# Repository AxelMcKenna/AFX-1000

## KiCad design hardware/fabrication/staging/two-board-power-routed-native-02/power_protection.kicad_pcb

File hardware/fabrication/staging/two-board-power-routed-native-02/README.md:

# Power board — first clean copper restoration

This checkpoint restores 50 source nets while keeping all 1,090 component
values, the TBP10 schematic and all 1,105 footprint placements unchanged.
It closes **56 connections**, reducing power-board opens from **2,709 to 2,653**.
It is the current power-board development checkpoint, not a fabrication release.

| Check | Result |
| --- | --- |
| Restored tracks / through vias | 1,689 / 68 |
| Restored source terminal groups | 50, all native-connected |
| Power-board opens | 2,653 |
| Geometry / schematic parity / ERC errors | 0 / 0 / 0 |
| Retained isolated-reference ERC warnings | 2 |
| Component or placement changes | None |
| Source zones/planes imported | None |

The [native check](review.json) enables every rule category. The
[independent copper audit](copper-audit.json) compares actual source and target
track geometry, layer, width, via drill/span, net identity and native physical
pad connections. It verifies every restored connection group, all footprint
geometries and the unchanged schematic partition. It also rechecks the module
branch, 32 fault/reset cases, two source-sense channels and 64 UV cases.

## Selection and rejected trial

The source boards remain useful where every terminal of a net retains the same
translation, orientation and land shape. Nets split by the new protection
logic are excluded. Moving a single terminal excludes its old net copper from
automatic restoration; plane nets are also excluded.

The [first trial](../two-board-power-routed-native-01/review.json) restored 102
candidate nets but failed 1,046 native geometry checks. These included copper
and hole clearances, shorts, mask bridges, old track widths and old drill sizes.
All findings touched 52 candidate nets. This checkpoint excludes those complete
nets instead of weakening current rules. Their routes still require deliberate
repair or replacement. The failed trial is retained for diagnosis.

The 50 accepted nets come from supply (2), inlet (2), disconnect/protection (29),
monitor (3) and negative-startup (14) sources. The
[restoration ledger](copper-restoration.json) identifies every terminal and copper
object. Every accepted terminal set is fully connected in the native board;
that is verified separately from the constructor's selection logic.

Through vias retain their physical front/back endpoints and drill dimensions
on the provisional eight-layer board. Extra enabled inner layers change their
native layer bitmask; the audit compares the actual through-via span rather
than requiring an old six-layer bitmask. This does not qualify the physical
stack, copper weights, return paths or electrical behavior of the converted
layer arrangement. Native schematic-path annotations are excluded from the
geometry comparison; component positions, pad shapes and board setup are not.

## Actual native copper views

All eight native exports were visually inspected. The bottom view uses the
same top-view coordinates, not a mirrored assembly view. Copper-only plots
show the remaining routing clearly; they are not assembly drawings.

| Front copper | Back copper |
| --- | --- |
|  |  |

Native inner exports: [In1](plots/inner1.svg), [In2](plots/inner2.svg),
[In3](plots/inner3.svg), [In4](plots/inner4.svg), [In5](plots/inner5.svg),
[In6](plots/inner6.svg).

## Remaining fabrication work

The [TBP10 module circuit](../two-board-power-native-10/README.md) and its
[first-article procedure](../two-board-power-native-10/MODULE-FIRST-ARTICLE.md)
remain applicable. Its protection cell and return star are still unrouted.
Individual module containment, supported startup/current bounds, passive BOM,
critical placement and thermal RTN vias remain unfinished.

The [fuse voltage-budget screen](../two-board-module-protection-followup-01/review.json)
finds only 0.354 V of remaining steady-state series-drop allocation. Two reviewed
250 mA candidate fuse families exceed that at rated current; neither has been
inserted into the PCB. Actual lower-current behavior, temperature derating and
startup coordination must be supported before choosing a part or revising the
UV window. This is a design decision still to make, not an adopted fuse circuit.

The signal board remains at 251 opens with its missing ESS codec footprint.
The power board still needs 2,653 connections, final interfaces, loaded supply/
reference/enable checks and fault timing work. Manufacturing stack/BOM/process,
complete fabrication outputs, cooling/supports and full installed housing fit
also remain unfinished. No board order or fabrication release was issued.

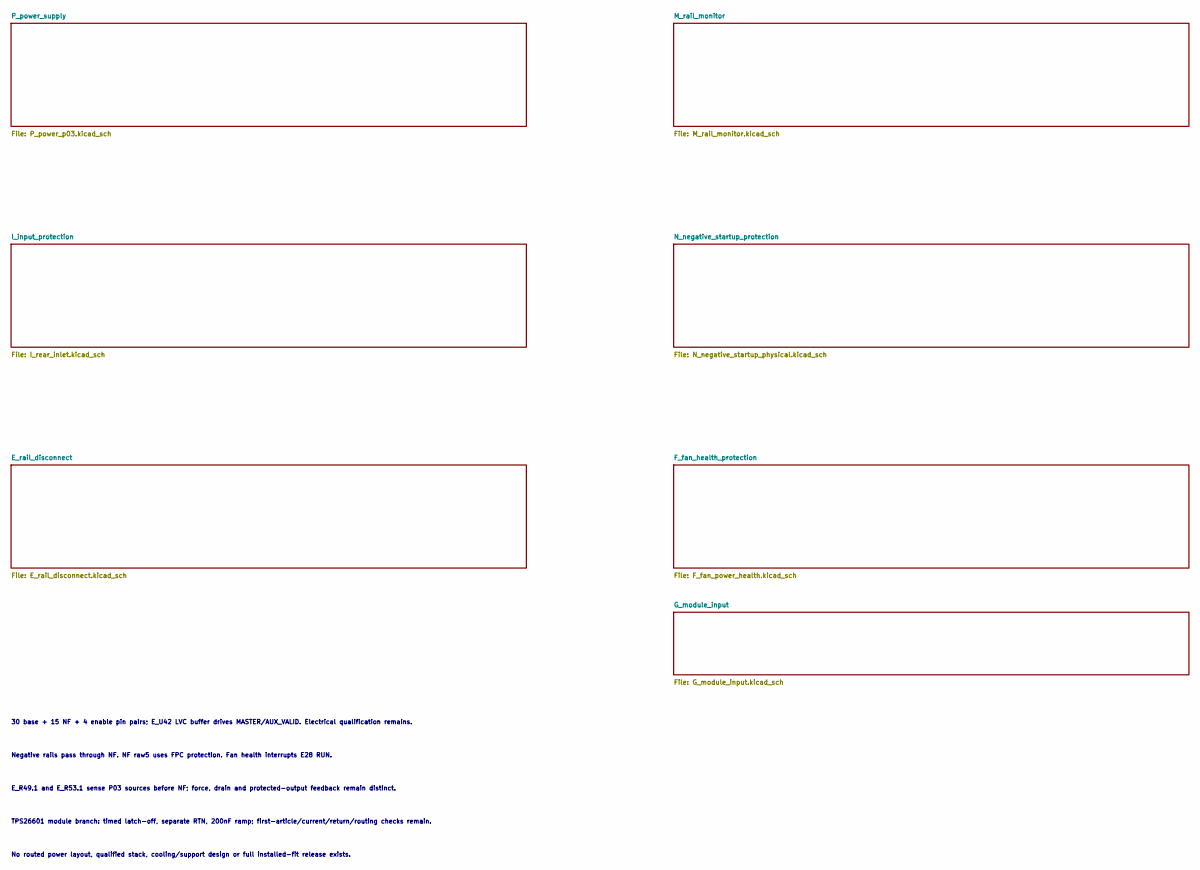
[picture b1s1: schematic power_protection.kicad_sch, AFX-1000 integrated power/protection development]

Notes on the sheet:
30 base + 15 NF + 4 enable pin pairs; E_U42 LVC buffer drives MASTER/AUX_VALID. Electrical qualification remains.
Negative rails pass through NF. NF raw5 uses FPC protection. Fan health interrupts E28 RUN.
E_R49.1 and E_R53.1 sense P03 sources before NF; force, drain and protected-output feedback remain distinct.
TPS26601 module branch: timed latch-off, separate RTN, 200nF ramp; first-article/current/return/routing checks remain.
No routed power layout, qualified stack, cooling/support design or full installed-fit release exists.

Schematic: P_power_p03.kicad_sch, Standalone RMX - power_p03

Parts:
P_C1, P_C63: 10uF 63V X7R; C_1210_3225Metric
P_C2, P_C3, P_C5, P_C6, P_C8, P_C9, P_C37, P_C42, P_C52, P_C57, P_C64, P_C65, P_C67, P_C68, P_C70, P_C204, P_C205, P_C224, P_C225, P_C254: 22uF 50V X7R 20% TDK C3225X7R1H226M250AC; C_1210_3225Metric
P_C4, P_C7, P_C10, P_C35, P_C38, P_C40, P_C43, P_C50, P_C53, P_C55, P_C58, P_C59, P_C61, P_C66, P_C69, P_C71: 100nF 50V X7R; C_0805_2012Metric
P_C11, P_C30, P_C107, P_C108: 100nF 16V X7R; C_0805_2012Metric
P_C12, P_C14, P_C73, P_C75: 68pF 50V C0G 5%; C_0805_2012Metric
P_C13, P_C15, P_C74, P_C76: 330nF 16V X7R; C_0805_2012Metric
P_C31: 2.2uF 16V X7R; C_0805_2012Metric
P_C32, P_C33: 1uF film 63V 10% MKS2C041001F00KSSD; C_Rect_L7.2mm_W5.0mm_P5.00mm
P_C34, P_C39, P_C49, P_C54, P_C240: 47nF 50V C0G 5%; C_1210_3225Metric
P_C36, P_C41, P_C51, P_C56: 10uF 50V X7R; C_1210_3225Metric
P_C60, P_C62, P_C105: 1uF 50V X7R; C_0805_2012Metric
P_C72, P_C210, P_C211, P_C230, P_C231: 100nF 50V X7R 10% TDK C1005X7R1H104K050BB; C_0402_1005Metric
P_C101, P_C102: 2.2uF 100V X7R; C_1210_3225Metric
P_C103: 220uF 35V electrolytic 20% (EEUFR1V221); CP_Radial_D8.0mm_P3.50mm
P_C104: 1uF 50V X7R; C_1210_3225Metric
P_C106: 10uF 25V X7R 10% TDK C3225X7R1E106K250AC; C_1210_3225Metric
P_C109: 1nF 16V C0G 5%; C_0805_2012Metric
P_C110: 10nF 25V C0G 5% KEMET C0603C103J3GACTU; C_0603_1608Metric
P_C113: 1uF 100V X7S 10% TDK C2012X7S2A105K125AE; C_0805_2012Metric
P_C200, P_C220: 4.7uF 25V X7R 10% TDK C2012X7R1E475K125AB; C_0805_2012Metric
P_C201, P_C221, P_C255, P_C301, P_C302: 100nF 50V X7R; C_0603_1608Metric
P_C202, P_C203, P_C222, P_C223: 2.2uF 50V X7R 10% TDK C2012X7R1H225K125AC; C_0805_2012Metric
P_C206, P_C207, P_C208, P_C209, P_C226, P_C227, P_C228, P_C229: 47uF 25V X7S 20% TDK C3225X7S1E476M250AC; C_1210_3225Metric
P_C241: 1uF 25V X7R; C_1210_3225Metric
P_C242, P_C243, P_C244, P_C245, P_C246, P_C247, P_C248, P_C249, P_C250, P_C251: 100nF 25V C0G 5% KEMET C1206C104J3GACTU; C_1206_3216Metric
P_C252, P_C253: 1uF 16V X7R; C_1210_3225Metric
P_C300: 10nF 50V C0G 5%; C_0805_2012Metric
P_C401, P_C402: 100nF 50V X7R C0603C104K5RACTU; C0603
P_C403: 10nF 50V C0G C0603C103J5GACTU; C0603
P_D1, P_D2, P_D3, P_D4, P_D103: SS16-E3/61T; D_SMA
P_D101: SMBJ33CA-E3/52; D_SMB
P_D102: BAS116,215; SOT-23
P_J2: Header6; PinHeader_1x06_P2.54mm_Vertical
P_J3: Header2; PinHeader_1x02_P2.54mm_Vertical
P_J20, P_J21, P_J23, P_J24: Wurth 7466003R M3 SMT; Wurth_7466003R
P_J22: P03 READY test; PinHeader_1x03_P2.54mm_Vertical
P_J103: Bare POWER_READY probe pads, no fitted header; Probe2_P2.54_D1
P_J104: JST B3B-XH-A (XHP-3/SXH-001T-P0.6); JST_XH_B3B-XH-A_1x03_P2.50mm_Vertical
P_J106: JST B4B-XH-A (XHP-4/SXH-001T-P0.6); JST_XH_B4B-XH-A_1x04_P2.50mm_Vertical
P_L1, P_L6: 33uH 20% SRP7050WA-330M; SRP7050WA
P_L2, P_L3, P_L7, P_L8: 68uH 20% SRP1050WA-680M; SRP1050WA
P_L20, P_L23: 4.7uH 20% Coilcraft XAL7030-472MEC; L_Coilcraft_XAL7030-472
P_Q101: PSMN012-100YL,115; LFPAK56
P_Q102: BSS138-7-F; SOT-23
P_Q103: DMN2056U-7; SOT-23
P_R1: 300k 0.01% 5ppm; R_0805_2012Metric
P_R2, P_R3, P_R4, P_R45, P_R46: 15k 0.01% 5ppm; R_0805_2012Metric
P_R5, P_R20, P_R21, P_R34, P_R35: 330k 0.01% 5ppm; R_0805_2012Metric
P_R6, P_R7, P_R49, P_R50: 4.7k 1%; R_0805_2012Metric
P_R17, P_R19, P_R110: 1k 1%; R_0805_2012Metric
P_R18, P_R120: 100k 1%; R_0805_2012Metric
P_R22, P_R27, P_R36, P_R41, P_R243, P_R244: 100k 0.01% 5ppm; R_0805_2012Metric
P_R23, P_R28, P_R37, P_R42, P_R241: 6.8k 1%; R_0805_2012Metric
P_R24, P_R38: 9.09k 1%; R_0805_2012Metric
P_R25, P_R39, P_R47, P_R306: 200k 0.01% 5ppm; R_0805_2012Metric
P_R26, P_R40, P_R308: 180k 0.01% 5ppm; R_0805_2012Metric
P_R29, P_R43: 5.62k 1%; R_0805_2012Metric
P_R44: 240k 0.01% 5ppm; R_0805_2012Metric
P_R48, P_R301, P_R303, P_R305, P_R307, P_R309, P_R314: 10k 0.01% 5ppm; R_0805_2012Metric
P_R101, P_R103, P_R117: 309k 0.1% 10ppm; R_0805_2012Metric
P_R102: 40.2k 0.1% 10ppm; R_0805_2012Metric
P_R104: 28k 0.1% 10ppm; R_0805_2012Metric
P_R105: 68.1k 0.1% 10ppm; R_0805_2012Metric
P_R106, P_R109, P_R118, P_R119: 10k 0.1% 10ppm; R_0805_2012Metric
P_R107: 4.02k 0.1% 10ppm; R_0805_2012Metric
P_R108: 11.7k 0.1% 10ppm; R_0805_2012Metric
P_R111, P_R204, P_R224, P_R246: 10k 1%; R_0805_2012Metric
P_R112, P_R114: 47k 1%; R_0805_2012Metric
P_R113: 3.3k 1%; R_0805_2012Metric
P_R115: 30.9k 0.1% 10ppm; R_0805_2012Metric
P_R116: 3.09k 0.1% 10ppm; R_0805_2012Metric
P_R121: 100 1%; R_0805_2012Metric
P_R130: 49.9 0.01% 5ppm; R_0805_2012Metric
P_R200: 9k 0.01% 2ppm Susumu RG2012L-902-L-T1; R_0805_2012Metric
P_R201: 1k 0.01% 2ppm Susumu RG2012L-102-L-T1; R_0805_2012Metric
P_R202, P_R222: 24.3k 1%; R_0805_2012Metric
P_R203, P_R223: 18.2k 0.1% 25ppm Panasonic ERA6AEB1822V; R_0805_2012Metric
P_R205, P_R225: 22k 1%; R_0805_2012Metric
P_R206: 54.9 0.1% 25ppm Panasonic ERA6AEB549V; R_0805_2012Metric
P_R220: 11k 0.01% 5ppm; R_0805_2012Metric
P_R221, P_R311: 1k 0.01% 5ppm; R_0805_2012Metric
P_R240: 100 0.01% 5ppm; R_0805_2012Metric
P_R242: 120 0.01% 5ppm; R_0805_2012Metric
P_R245: 2.21k 1%; R_0805_2012Metric
P_R300, P_R302: 87.6k 0.01% 5ppm; R_0805_2012Metric
P_R304: 324k 0.01% 5ppm; R_0805_2012Metric
P_R310: 590 0.01% 5ppm; R_0805_2012Metric
P_R312: 7.5k 0.01% 5ppm; R_0805_2012Metric
P_R313: 1M 0.01% 5ppm; R_0805_2012Metric
P_R315: 750k 0.01% 5ppm; R_0805_2012Metric
P_R316: 2.2k 0.1% 25ppm Panasonic ERA6AEB222V; R_0805_2012Metric
P_R401: 100k ohm TNPW0805100KBEEA; R0805
P_R402: 10M 1% CRCW080510M0FKEA; R0805
P_R403: 1k 1% CRCW12061K00FKEA; R1206
P_U1, P_U13: LT3471EDD#PBF; DFN-10-1EP_3x3mm_P0.5mm_EP1.65x2.38mm
P_U4: REF5025EIDR; SOIC-8_3.9x4.9mm_P1.27mm
P_U5: OPA4192ID; SOIC-14_3.9x8.7mm_P1.27mm
P_U6, P_U24: OPA2192ID; SOIC-8_3.9x4.9mm_P1.27mm
P_U7: LT3080IMS8E#PBF; MSOP-8-1EP_3x3mm_P0.65mm_EP1.68x1.88mm
P_U8: LT3080IQ#PBF; TO-263-5_TabPin3
P_U10, P_U11: LT3090IDD#PBF; DFN-10-1EP_3x3mm_P0.5mm_EP1.65x2.38mm
P_U12: LT1634AIS8-2.5#PBF; SOIC-8_3.9x4.9mm_P1.27mm
P_U20, P_U23: TPS543620RPYR; TPS543620_RPY0014A
P_U21: ADR4550BRZ; SOIC-8_3.9x4.9mm_P1.27mm
P_U22: LT3045IDD#PBF; DFN-10-1EP_3x3mm_P0.5mm_EP1.65x2.38mm
P_U25: LTC2910HGN#PBF; SSOP-16_3.9x4.9mm_P0.635mm
P_U26: SN74LVC1G97DBVR; SOT-23-6
P_U101: TPS26630RGER; Texas_RGE0024H_VQFN-24-1EP_4x4mm_P0.5mm_EP2.7x2.7mm
P_U102: TPS7A1601DGNR; MSOP-8-1EP_3x3mm_P0.65mm_EP1.68x1.88mm
P_U103: TLV7011DBVR; SOT-23-5
P_U201: TPS389001DSET; TI_DSE0006A
P_U202: SN74AUP1G17DCKR; TI_DCK0005A

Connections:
/P_power_supply/AUX_FB: P_R109.1, P_R130.2, P_U102.2 (FB)
/P_power_supply/AUX_START_DELAY: P_C110.1 (+), P_U102.7 (DELAY)
/P_power_supply/AX03_RUN_DRIVE: P_R403.1, P_U202.4 (Y)
/P_power_supply/AX03_SOURCE_CT: P_C403.1, P_U201.5 (CT)
/P_power_supply/AX03_SOURCE_RESET: P_R401.2, P_R402.1, P_U201.6 (RESET_N), P_U202.2 (A)
/P_power_supply/BLOCK_DRV: P_Q102.1 (GATE), P_U101.4 (DRV)
/P_power_supply/BLOCK_GATE: P_Q101.4 (GATE), P_Q102.3 (DRAIN), P_U101.3 (B_GATE)
/P_power_supply/CUK_NODE: P_C1.2, P_D2.2 (A), P_L3.1
/P_power_supply/FAST_OV_GATE: P_Q103.1 (GATE), P_R120.1, P_R121.2
/P_power_supply/FAST_OV_OUT: P_R117.1, P_R121.1, P_U103.1 (OUT)
/P_power_supply/FAST_OV_REF: P_C109.1 (+), P_R118.2, P_R119.1, P_U103.4 (IN-)
/P_power_supply/FAST_OV_SENSE: P_R115.2, P_R116.1, P_R117.2, P_U103.3 (IN+)
/P_power_supply/INPUT_ILIM: P_R107.1, P_U101.10 (ILIM)
/P_power_supply/INPUT_OV: P_D102.1 (ANODE), P_R103.2, P_R104.1, P_U101.7 (OVP)
/P_power_supply/INPUT_PGTH: P_R105.2, P_R106.1, P_U101.15 (PGTH)
/P_power_supply/INPUT_SLEW: P_C105.1 (+), P_U101.9 (dVdT)
/P_power_supply/INPUT_UV: P_R101.2, P_R102.1, P_U101.6 (UVLO)
/P_power_supply/LO_CUK_NODE: P_C63.2, P_D4.2 (A), P_L8.1
/P_power_supply/LO_N_FB: P_C75.2, P_R46.2, P_R47.1, P_U13.4 (FB2P)
/P_power_supply/LO_N_RMID: P_R47.2, P_R48.1
/P_power_supply/LO_N_SS: P_C76.1, P_R50.2, P_U13.7 (SHDN_SS2)
/P_power_supply/LO_N_SW: P_C63.1, P_L7.2, P_U13.6 (SW2)
/P_power_supply/LO_P_FB: P_C73.2, P_R44.2, P_R45.1, P_U13.1 (FB1N)
/P_power_supply/LO_P_SS: P_C74.1, P_R49.2, P_U13.9 (SHDN_SS1)
/P_power_supply/LO_P_SW: P_D3.2 (A), P_L6.2, P_U13.10 (SW1)
/P_power_supply/LO_REF_1V: P_C72.1, P_R46.1, P_U13.2 (FB1P), P_U13.3 (VREF)
/P_power_supply/N12_DRIVE: P_C54.1, P_R42.1, P_U6.7 (OUT)
/P_power_supply/N12_FB: P_C54.2, P_R40.2, P_R41.1, P_U6.6 (-)
/P_power_supply/N12_RMID: P_R39.2, P_R40.1
/P_power_supply/N12_SET: P_C55.1, P_R39.1, P_R42.2, P_U11.4 (SET)
/P_power_supply/N19_DRIVE: P_C49.1, P_R37.1, P_U6.1 (OUT)
/P_power_supply/N19_FB: P_C49.2, P_R35.2, P_R36.1, P_U6.2 (-)
/P_power_supply/N19_RMID: P_R34.2, P_R35.1
/P_power_supply/N19_SET: P_C50.1, P_R34.1, P_R37.2, P_U10.4 (SET)
/P_power_supply/NREF_2V5: P_R18.1, P_R19.1, P_U12.4 (GND/ANODE), P_U12.5 (TEST)
/P_power_supply/NREF_FILTER: P_C33.1, P_R19.2, P_U6.3 (+), P_U6.5 (+)
/P_power_supply/P03_ANA_DIV: P_R242.2, P_R243.1, P_R244.1
/P_power_supply/P03_ANA_DRIVE: P_C240.1 (+), P_R241.1, P_U24.1 (OUT_A)
/P_power_supply/P03_ANA_FB: P_C240.2 (-), P_R244.2, P_U24.2 (IN_A_N)
/P_power_supply/P03_ANA_SET: P_C241.1 (+), P_R241.2, P_R242.1, P_U22.7 (SET)
/P_power_supply/P03_AUX_TRIM: P_R108.2, P_R130.1
/P_power_supply/P03_A_BOOT: P_C221.1 (+), P_U23.14 (BOOT)
/P_power_supply/P03_A_BP5: P_C220.1 (+), P_U23.6 (BP5)
/P_power_supply/P03_A_ENABLE: P_R224.2, P_R225.1, P_U23.7 (EN)
/P_power_supply/P03_A_FB: P_R220.2, P_R221.1, P_U23.4 (FB)
/P_power_supply/P03_A_FSEL: P_R222.1, P_U23.1 (SYNC_FSEL)
/P_power_supply/P03_A_MODE: P_R223.1, P_U23.2 (MODE)
/P_power_supply/P03_A_SW: P_C221.2 (-), P_L23.1 (SW), P_U23.10 (SW), P_U23.13 (SW_BOOT_RETURN)
/P_power_supply/P03_D_BOOT: P_C201.1 (+), P_U20.14 (BOOT)
/P_power_supply/P03_D_BP5: P_C200.1 (+), P_U20.6 (BP5)
/P_power_supply/P03_D_ENABLE: P_R204.2, P_R205.1, P_U20.7 (EN)
/P_power_supply/P03_D_FB: P_R201.1, P_R206.2, P_U20.4 (FB)
/P_power_supply/P03_D_FB_TRIM: P_R200.2, P_R206.1
/P_power_supply/P03_D_FSEL: P_R202.1, P_U20.1 (SYNC_FSEL)
/P_power_supply/P03_D_MODE: P_R203.1, P_U20.2 (MODE)
/P_power_supply/P03_D_SW: P_C201.2 (-), P_L20.1 (SW), P_U20.10 (SW), P_U20.13 (SW_BOOT_RETURN)
/P_power_supply/P03_MON_ANA: P_R302.2, P_R303.1, P_U25.2 (V2)
/P_power_supply/P03_MON_BUCK_OK: P_U25.5 (V5), P_U26.4 (Y)
/P_power_supply/P03_MON_DIG: P_R300.2, P_R301.1, P_U25.1 (V1)
/P_power_supply/P03_MON_N12: P_R314.2, P_R315.1, P_U25.8 (V8)
/P_power_supply/P03_MON_N19: P_R312.2, P_R313.1, P_U25.7 (V7)
/P_power_supply/P03_MON_NEG_BIAS: P_R310.2, P_R311.1, P_R312.1, P_R314.1
/P_power_supply/P03_MON_P12: P_R306.2, P_R307.1, P_U25.4 (V4)
/P_power_supply/P03_MON_P19: P_R304.2, P_R305.1, P_U25.3 (V3)
/P_power_supply/P03_MON_REF: P_R310.1, P_U25.10 (REF)
/P_power_supply/P03_MON_TIMER: P_C300.1 (+), P_U25.15 (TMR)
/P_power_supply/P03_MON_VIN: P_R308.2, P_R309.1, P_U25.6 (V6)
/P_power_supply/P03_PRE6V: P_C226.1 (+), P_C227.1 (+), P_C228.1 (+), P_C229.1 (+), P_C253.1 (+), P_L23.2 (OUT), P_R220.1, P_U21.2 (VIN), P_U22.1 (IN), P_U22.2 (IN), P_U22.3 (EN_UV), P_U22.6 (PGFB)
/P_power_supply/P03_REF5: P_C252.1 (+), P_R240.1, P_U21.6 (VOUT)
/P_power_supply/P03_REF_FILTER: P_C242.1 (+), P_C243.1 (+), P_C244.1 (+), P_C245.1 (+), P_C246.1 (+), P_C247.1 (+), P_C248.1 (+), P_C249.1 (+), P_C250.1 (+), P_C251.1 (+), P_R240.2, P_U24.3 (IN_A_P)
/P_power_supply/P03_SOURCES_READY: P_R246.2, P_U20.3 (PGOOD), P_U23.3 (PGOOD), P_U26.3 (In0)
/P_power_supply/P03_SPARE_24: P_U24.6 (IN_B_N), P_U24.7 (OUT_B)
/P_power_supply/P03_SPARE_C: P_U5.8 (OUT), P_U5.9 (-)
/P_power_supply/P12_DRIVE: P_C39.1, P_R28.1, P_U5.7 (OUT)
/P_power_supply/P12_FB: P_C39.2, P_R26.2, P_R27.1, P_U5.6 (-)
/P_power_supply/P12_RMID: P_R25.2, P_R26.1
/P_power_supply/P12_SET: P_C40.1, P_R25.1, P_R28.2, P_U8.2 (SET)
/P_power_supply/P19_DRIVE: P_C34.1, P_R23.1, P_U5.1 (OUT)
/P_power_supply/P19_FB: P_C34.2, P_R21.2, P_R22.1, P_U5.2 (-)
/P_power_supply/P19_RMID: P_R20.2, P_R21.1
/P_power_supply/P19_SET: P_C35.1, P_R20.1, P_R23.2, P_U7.4 (SET)
/P_power_supply/POWER_READY: P_J22.3 (POWER_READY), P_J103.2 (POWER_READY), P_R110.2, P_R204.1, P_R224.1, P_U26.6 (In2), P_U101.16 (PGOOD)
/P_power_supply/PREF_2V5: P_C31.1, P_R17.1, P_U4.6 (VOUT)
/P_power_supply/PREF_FILTER: P_C32.1, P_R17.2, P_U5.3 (+), P_U5.5 (+)
/P_power_supply/RAW_N17: P_C56.1, P_C67.1, P_C68.1, P_C69.1, P_C75.1, P_L8.2, P_R48.2, P_U11.8 (ILIM), P_U11.9 (IN), P_U11.10 (IN), P_U11.11 (EP/IN)
/P_power_supply/RAW_N22: P_C8.1, P_C9.1, P_C10.1, P_C14.1, P_C51.1, P_C61.1, P_C62.1, P_L3.2, P_R5.2, P_R18.2, P_U6.4 (V-), P_U10.8 (ILIM), P_U10.9 (IN), P_U10.10 (IN), P_U10.11 (EP/IN)
/P_power_supply/RAW_N_FB: P_C14.2, P_R4.2, P_R5.1, P_U1.4 (FB2P)
/P_power_supply/RAW_N_SS: P_C15.1, P_R7.2, P_U1.7 (SHDN_SS2)
/P_power_supply/RAW_N_SW: P_C1.1, P_L2.2, P_U1.6 (SW2)
/P_power_supply/RAW_P17: P_C41.1, P_C64.1, P_C65.1, P_C66.1, P_C73.1, P_D3.1 (K), P_R44.1, P_U8.4 (VCONTROL), P_U8.5 (IN)
/P_power_supply/RAW_P22: P_C5.1, P_C6.1, P_C7.1, P_C12.1, P_C36.1, P_C59.1, P_C60.1, P_D1.1 (K), P_R1.1, P_U5.4 (V+), P_U7.5 (VCONTROL), P_U7.7 (IN), P_U7.8 (IN)
/P_power_supply/RAW_P_FB: P_C12.2, P_R2.2, P_R3.1, P_U1.1 (FB1N)
/P_power_supply/RAW_P_RMID: P_R1.2, P_R2.1
/P_power_supply/RAW_P_SS: P_C13.1, P_R6.2, P_U1.9 (SHDN_SS1)
/P_power_supply/RAW_P_SW: P_D1.2 (A), P_L1.2, P_U1.10 (SW1)
/P_power_supply/SPARE_OUT: P_U5.13 (SPARE-), P_U5.14 (SPARE_OUT)
/P_power_supply/SW_REF_1V: P_C11.1, P_R4.1, P_U1.2 (FB1P), P_U1.3 (VREF)
/P_power_supply/VIN_IC: P_C102.1 (+), P_C113.1 (+), P_Q101.5 (DRAIN/MB), P_R115.1, P_U101.1 (IN), P_U101.2 (IN), P_U102.5 (EN), P_U102.8 (IN)
PWR_5V_DIG_SRC: P_C30.1, P_C206.1 (+), P_C207.1 (+), P_C208.1 (+), P_C209.1 (+), P_J3.1 (5V_DIG), P_J23.1, P_L20.2 (OUT), P_R6.1, P_R7.1, P_R49.1, P_R50.1, P_R200.1, P_R300.1, P_U4.1 (EN), P_U4.2 (VIN), P_U10.5 (SHDN), P_U11.5 (SHDN); also elsewhere on the board
PWR_AGND: P_C2.2, P_C3.2, P_C4.2, P_C5.2, P_C6.2, P_C7.2, P_C8.2, P_C9.2, P_C10.2, P_C11.2, P_C13.2, P_C15.2, P_C30.2, P_C31.2, P_C32.2, P_C33.2, P_C35.2, P_C36.2, P_C37.2, P_C38.2, P_C40.2, P_C41.2, P_C42.2, P_C43.2, P_C50.2, P_C51.2, P_C52.2, P_C53.2, P_C55.2, P_C56.2, P_C57.2, P_C58.2, P_C59.2, P_C60.2, P_C61.2, P_C62.2, P_C64.2, P_C65.2, P_C66.2, P_C67.2, P_C68.2, P_C69.2, P_C70.2, P_C71.2, P_C72.2, P_C74.2, P_C76.2, P_C101.2 (-), P_C102.2 (-), P_C103.2 (-), P_C104.2 (-), P_C105.2 (-), P_C106.2 (-), P_C107.2 (-), P_C108.2 (-), P_C109.2 (-), P_C110.2 (-), P_C113.2 (-), P_C200.2 (-), P_C202.2 (-), P_C203.2 (-), P_C204.2 (-), P_C205.2 (-), P_C206.2 (-), P_C207.2 (-), P_C208.2 (-), P_C209.2 (-), P_C210.2 (-), P_C211.2 (-), P_C220.2 (-), P_C222.2 (-), P_C223.2 (-), P_C224.2 (-), P_C225.2 (-), P_C226.2 (-), P_C227.2 (-), P_C228.2 (-), P_C229.2 (-), P_C230.2 (-), P_C231.2 (-), P_C241.2 (-), P_C242.2 (-), P_C243.2 (-), P_C244.2 (-), P_C245.2 (-), P_C246.2 (-), P_C247.2 (-), P_C248.2 (-), P_C249.2 (-), P_C250.2 (-), P_C251.2 (-), P_C252.2 (-), P_C253.2 (-), P_C254.2 (-), P_C255.2 (-), P_C300.2 (-), P_C301.2 (-), P_C302.2 (-), P_C401.2, P_C402.2, P_C403.2, P_D2.1 (K), P_D4.1 (K), P_D101.2, P_D103.2 (ANODE), P_J2.2 (AGND), P_J3.2 (AGND), P_J20.1, P_J21.1, P_J22.2 (AGND), P_J103.1 (AGND), P_J104.3 (AGND), P_J106.2 (AGND), P_Q103.2 (SOURCE), P_R3.2, P_R22.2, P_R24.2, P_R27.2, P_R29.2, P_R36.2, P_R38.2, P_R41.2, P_R43.2, P_R45.2, P_R102.2, P_R104.2, P_R106.2, P_R107.2, P_R109.2, P_R111.2, P_R112.2, P_R114.2, P_R116.2, P_R119.2, P_R120.2, P_R201.2, P_R202.2, P_R203.2, P_R205.2, P_R221.2, P_R222.2, P_R223.2, P_R225.2, P_R243.2, P_R245.2, P_R301.2, P_R303.2, P_R305.2, P_R307.2, P_R309.2, P_R311.2, P_R402.2, P_U1.5 (FB2N), P_U1.11 (GND_EP), P_U4.4 (GND), P_U5.10 (+), P_U5.11 (V-), P_U5.12 (SPARE+), P_U6.8 (V+), P_U10.3 (GND), P_U11.3 (GND), P_U12.6 (VOUT/CATHODE), P_U13.5 (FB2N), P_U13.11 (GND_EP), P_U20.5 (AGND), P_U20.9 (PGND), P_U20.11 (PGND), P_U21.4 (GND), P_U22.5 (ILIM), P_U22.8 (GND), P_U22.11 (EP_GND), P_U23.5 (AGND), P_U23.9 (PGND), P_U23.11 (PGND), P_U24.4 (V_N), P_U24.5 (IN_B_P), P_U25.9 (GND), P_U25.13 (DIS), P_U25.14 (SEL), P_U26.1 (In1_AND_CONFIG_LOW), P_U26.2 (GND), P_U101.8 (GND), P_U101.25 (EP/GND), P_U102.4 (GND), P_U102.9 (EP/GND), P_U103.2 (VEE), P_U201.2 (GND), P_U202.3 (GND); also elsewhere on the board
PWR_DC_IN: P_C101.1 (+), P_D101.1, P_Q101.1 (SOURCE), P_Q101.2 (SOURCE), P_Q101.3 (SOURCE), P_Q102.2 (SOURCE), P_R101.1, P_R103.1, P_U101.5 (IN_SYS); also elsewhere on the board
PWR_MODULE_FEED_IN: P_C2.1, P_C3.1, P_C4.1, P_C70.1, P_C71.1, P_C103.1 (+), P_C104.1 (+), P_C202.1 (+), P_C203.1 (+), P_C204.1 (+), P_C205.1 (+), P_C210.1 (+), P_C211.1 (+), P_C222.1 (+), P_C223.1 (+), P_C224.1 (+), P_C225.1 (+), P_C230.1 (+), P_C231.1 (+), P_C255.1 (+), P_D103.1 (CATHODE), P_L1.1, P_L2.1, P_L6.1, P_L7.1, P_R105.1, P_R114.1, P_R308.1, P_U1.8 (VIN), P_U13.8 (VIN), P_U20.8 (VIN), P_U20.12 (VIN), P_U23.8 (VIN), P_U23.12 (VIN), P_U24.8 (V_P), P_U101.17 (OUT), P_U101.18 (OUT); also elsewhere on the board
PWR_N12_SOURCE: P_C57.1, P_C58.1, P_J2.5 (N12), P_R43.1, P_R315.2, P_U11.1 (OUT), P_U11.2 (OUT); also elsewhere on the board
PWR_N19_SOURCE: P_C52.1, P_C53.1, P_J2.3 (N19), P_R38.1, P_R313.2, P_U10.1 (OUT), P_U10.2 (OUT); also elsewhere on the board
PWR_P03_SOURCES_READY: P_J22.1 (ALL_SOURCES_READY), P_J106.4 (SOURCE_READY), P_R316.2, P_U25.12 (RST_ACTIVE_LOW); also elsewhere on the board
PWR_P12_SRC: P_C42.1, P_C43.1, P_J2.4 (P12), P_R29.1, P_R306.1, P_U8.3 (OUT/TAB); also elsewhere on the board
PWR_P19_SRC: P_C37.1, P_C38.1, P_J2.1 (P19), P_R24.1, P_R304.1, P_U7.1 (OUT), P_U7.2 (OUT), P_U7.3 (OUT), P_U7.9 (EP/OUT); also elsewhere on the board
PWR_POWER_RUN: P_J104.2 (POWER_RUN), P_Q103.3 (DRAIN), P_R112.1, P_U101.12 (SHDN), P_U102.3 (PG), P_U201.1 (SENSE); also elsewhere on the board
PWR_RUN_BEFORE_FAN: P_J106.3 (POWER_RUN), P_R403.2; also elsewhere on the board
PWR_SWITCH_SUPPLY: P_J104.1 (SWITCH_SUPPLY), P_R113.2; also elsewhere on the board
PWR_V2V5_AUX: P_C106.1 (+), P_C107.1 (+), P_C108.1 (+), P_C301.1 (+), P_C302.1 (+), P_C401.1, P_C402.1, P_D102.3 (CATHODE), P_J106.1 (V2V5_AUX), P_R108.1, P_R110.1, P_R111.1, P_R113.1, P_R118.1, P_R246.1, P_R316.1, P_R401.1, P_U25.16 (VCC), P_U26.5 (VCC), P_U102.1 (OUT), P_U103.5 (VCC), P_U201.3 (MR), P_U201.4 (VDD), P_U202.5 (VCC); also elsewhere on the board
PWR_V5_REG_SRC: P_C254.1 (+), P_J2.6 (V5_REG), P_J24.1, P_R245.1, P_R302.1, P_U22.9 (OUTS), P_U22.10 (OUT); also elsewhere on the board

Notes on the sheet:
AX03 prototype: only J106.3 buffered; internal POWER_RUN, R113 and PG topology retained. No physical/fabrication release.

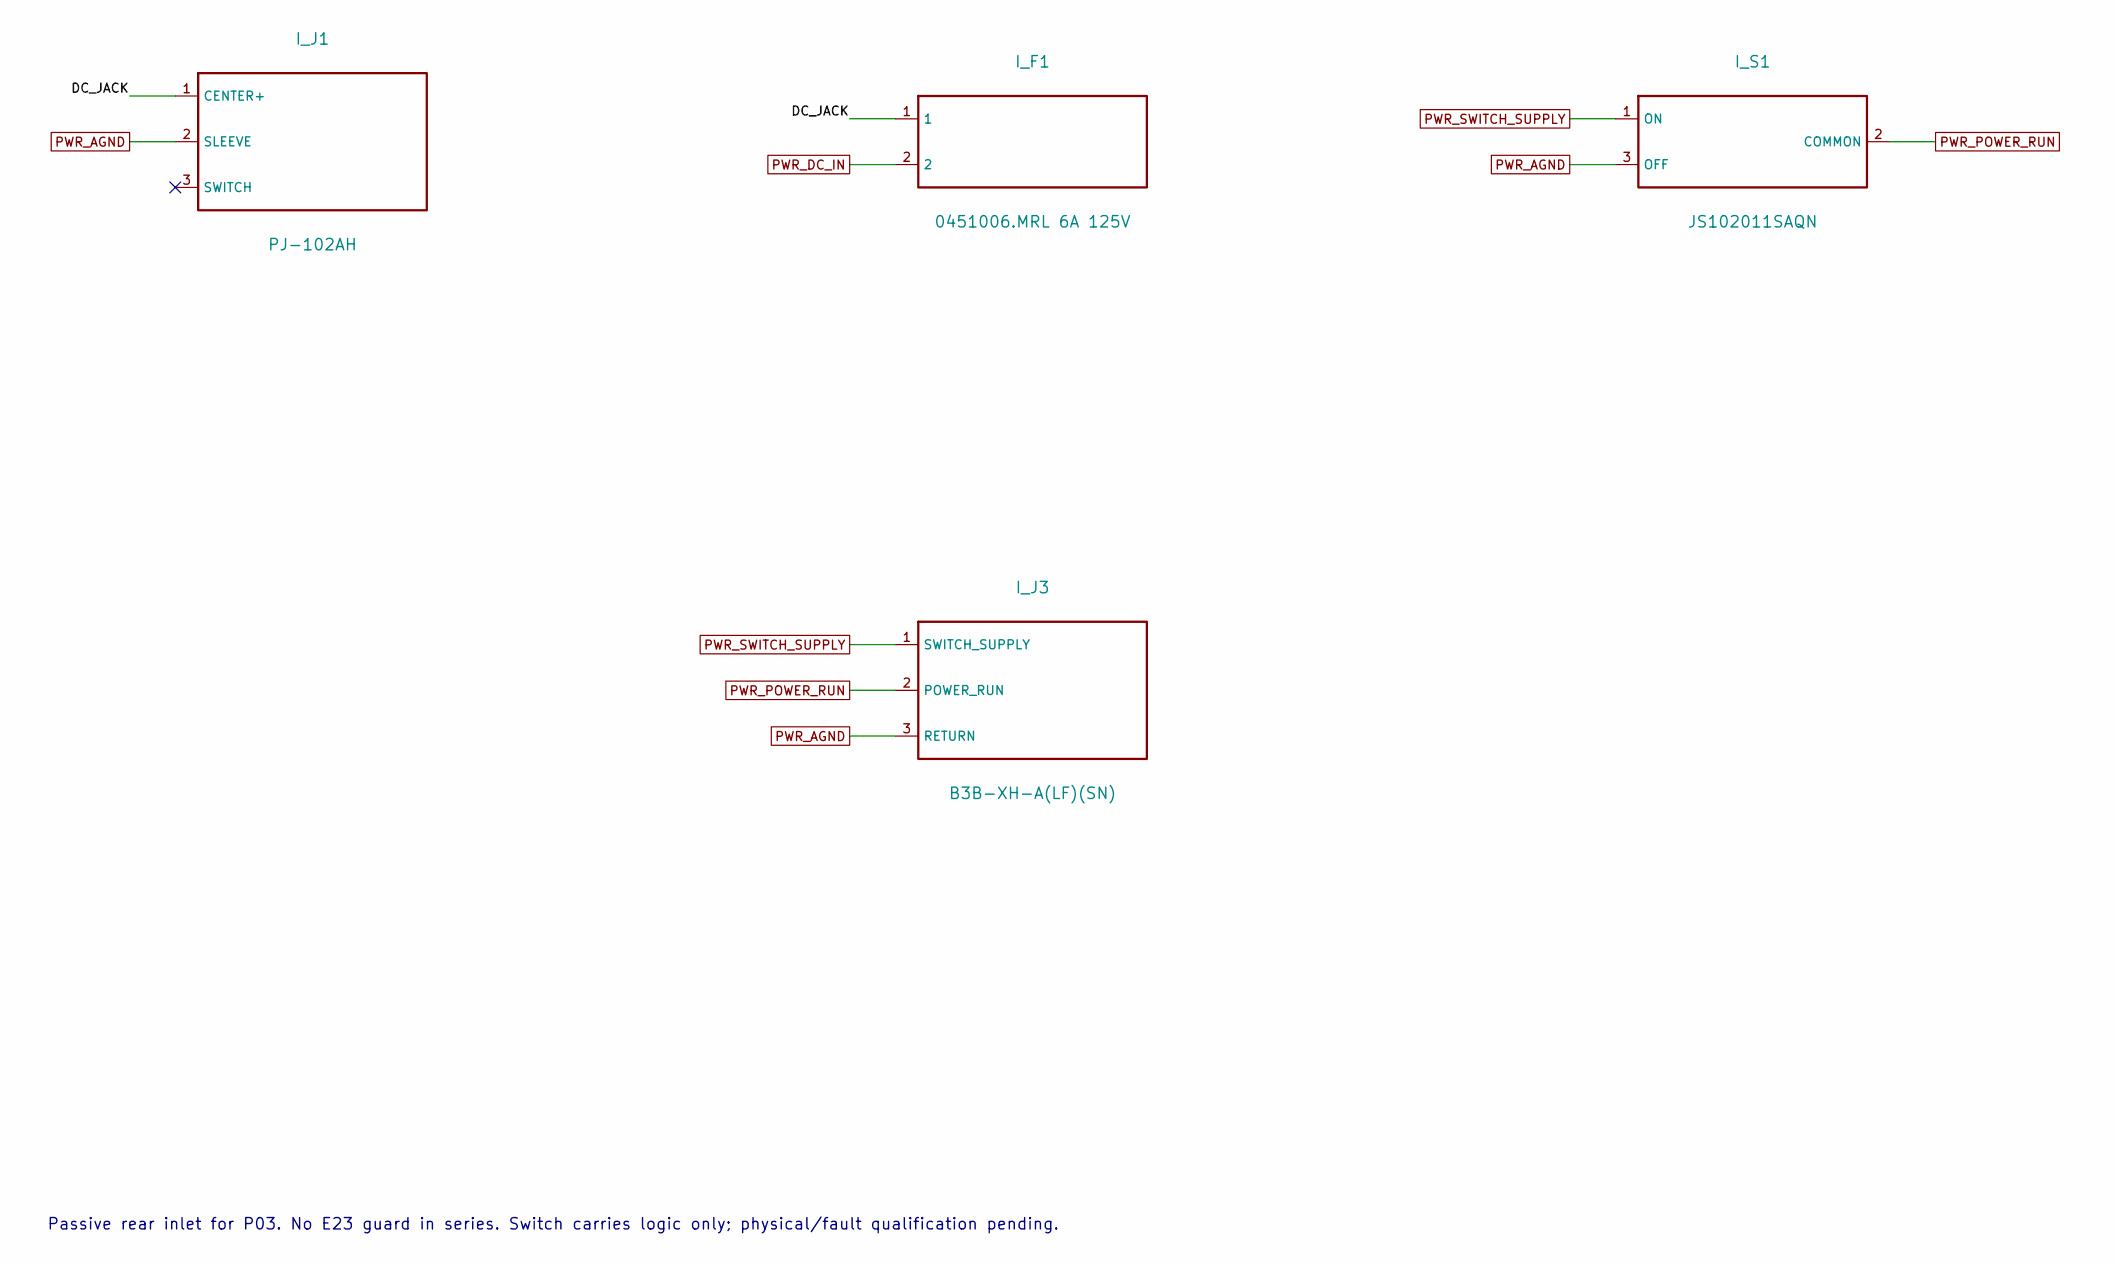
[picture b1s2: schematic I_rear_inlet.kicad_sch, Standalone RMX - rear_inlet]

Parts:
I_F1: 0451006.MRL 6A 125V; Fuse_Littelfuse-NANO2-451_453
I_J1: PJ-102AH; PJ102AH_RearEdge_E23
I_J3: B3B-XH-A(LF)(SN); JST_XH_B3B-XH-A_1x03_P2.50mm_Vertical
I_S1: JS102011SAQN; JS102011SAQN_RearEdge_E23

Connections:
/I_input_protection/DC_JACK: I_F1.1, I_J1.1 (CENTER+)
PWR_AGND: I_J1.2 (SLEEVE), I_J3.3 (RETURN), I_S1.3 (OFF); also elsewhere on the board
PWR_DC_IN: I_F1.2; also elsewhere on the board
PWR_POWER_RUN: I_J3.2 (POWER_RUN), I_S1.2 (COMMON); also elsewhere on the board
PWR_SWITCH_SUPPLY: I_J3.1 (SWITCH_SUPPLY), I_S1.1 (ON); also elsewhere on the board

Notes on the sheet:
Passive rear inlet for P03. No E23 guard in series. Switch carries logic only; physical/fault qualification pending.
